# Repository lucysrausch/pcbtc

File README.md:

#PCB based MIDI Tesla Coil

For documentation, please see (and like ;) my Hackaday project: https://hackaday.io/project/165112-pcbtc-gan-edition

For the mainboard, please use V1.6 to order the pcbs. Select the pcb thickness to be as thin as possible, eg. 1mm.
For the current design you also need the bottom pcb coil (https://github.com/lucysrausch/pcbtc/tree/master/hardware/gerber_coil_01) and the top pcb coil (https://github.com/lucysrausch/pcbtc/tree/master/hardware/gerber_coil_04).
For these pcbs, please use 1.6mm thickness or thicker (eg. 2mm).

Check out the interactive html BOM for easier assembly: https://github.com/lucysrausch/pcbtc/blob/master/hardware/kicad/bom/ibom.html

Known bugs (V1.5):
* Missing pulldown for gatedriver input of the flyback converter
This can cause problems when in DFU mode as the mosfet might switch on permanently, shortying VUSB (Fixed in V1.6)
* Missing input decoupling capacitors underneath the LMG5200.
Adding additional high-quality 100pF and 100nF ceramic capacitors on the bottom of the pcb improves performance drastically (Fixed in V1.6)
* Unknown problem causes GaN module to fail when touching the arcs with the finger or a screwdriver.
The reson for this is unknown so far. Maybe EMI, maybe bad layout. Just don't touch the arcs for too long for now. Discharges to air work reliably. (Maybe fixed in V1.6 thanks to suggestions from nikisalli)

Flash with dfu-util -d 0483:df11 -a 0 -s 0x8000000:leave -D build/pcbtcMIDI.bin

Midi stack based on:
https://github.com/keshikan/CureMIDI 

## USB-MIDI Interface (2IN/2OUT) for STM32 "CureMIDI"

### Author

(c) 2018 Keshikan ( [Website](http://www.keshikan.net/),  [Twitter](https://twitter.com/keshinomi_88pro) )

### License

* USB MIDI Class Driver: [CC BY 4.0](https://creativecommons.org/licenses/by/4.0/)
* STM32 CubeF0: BSD-3-Clause based.
* Other Codes, Hardware, Schematic: [GPLv3](https://www.gnu.org/licenses/gpl-3.0.html)

See also [LICENSE.md](./LICENSE.md)

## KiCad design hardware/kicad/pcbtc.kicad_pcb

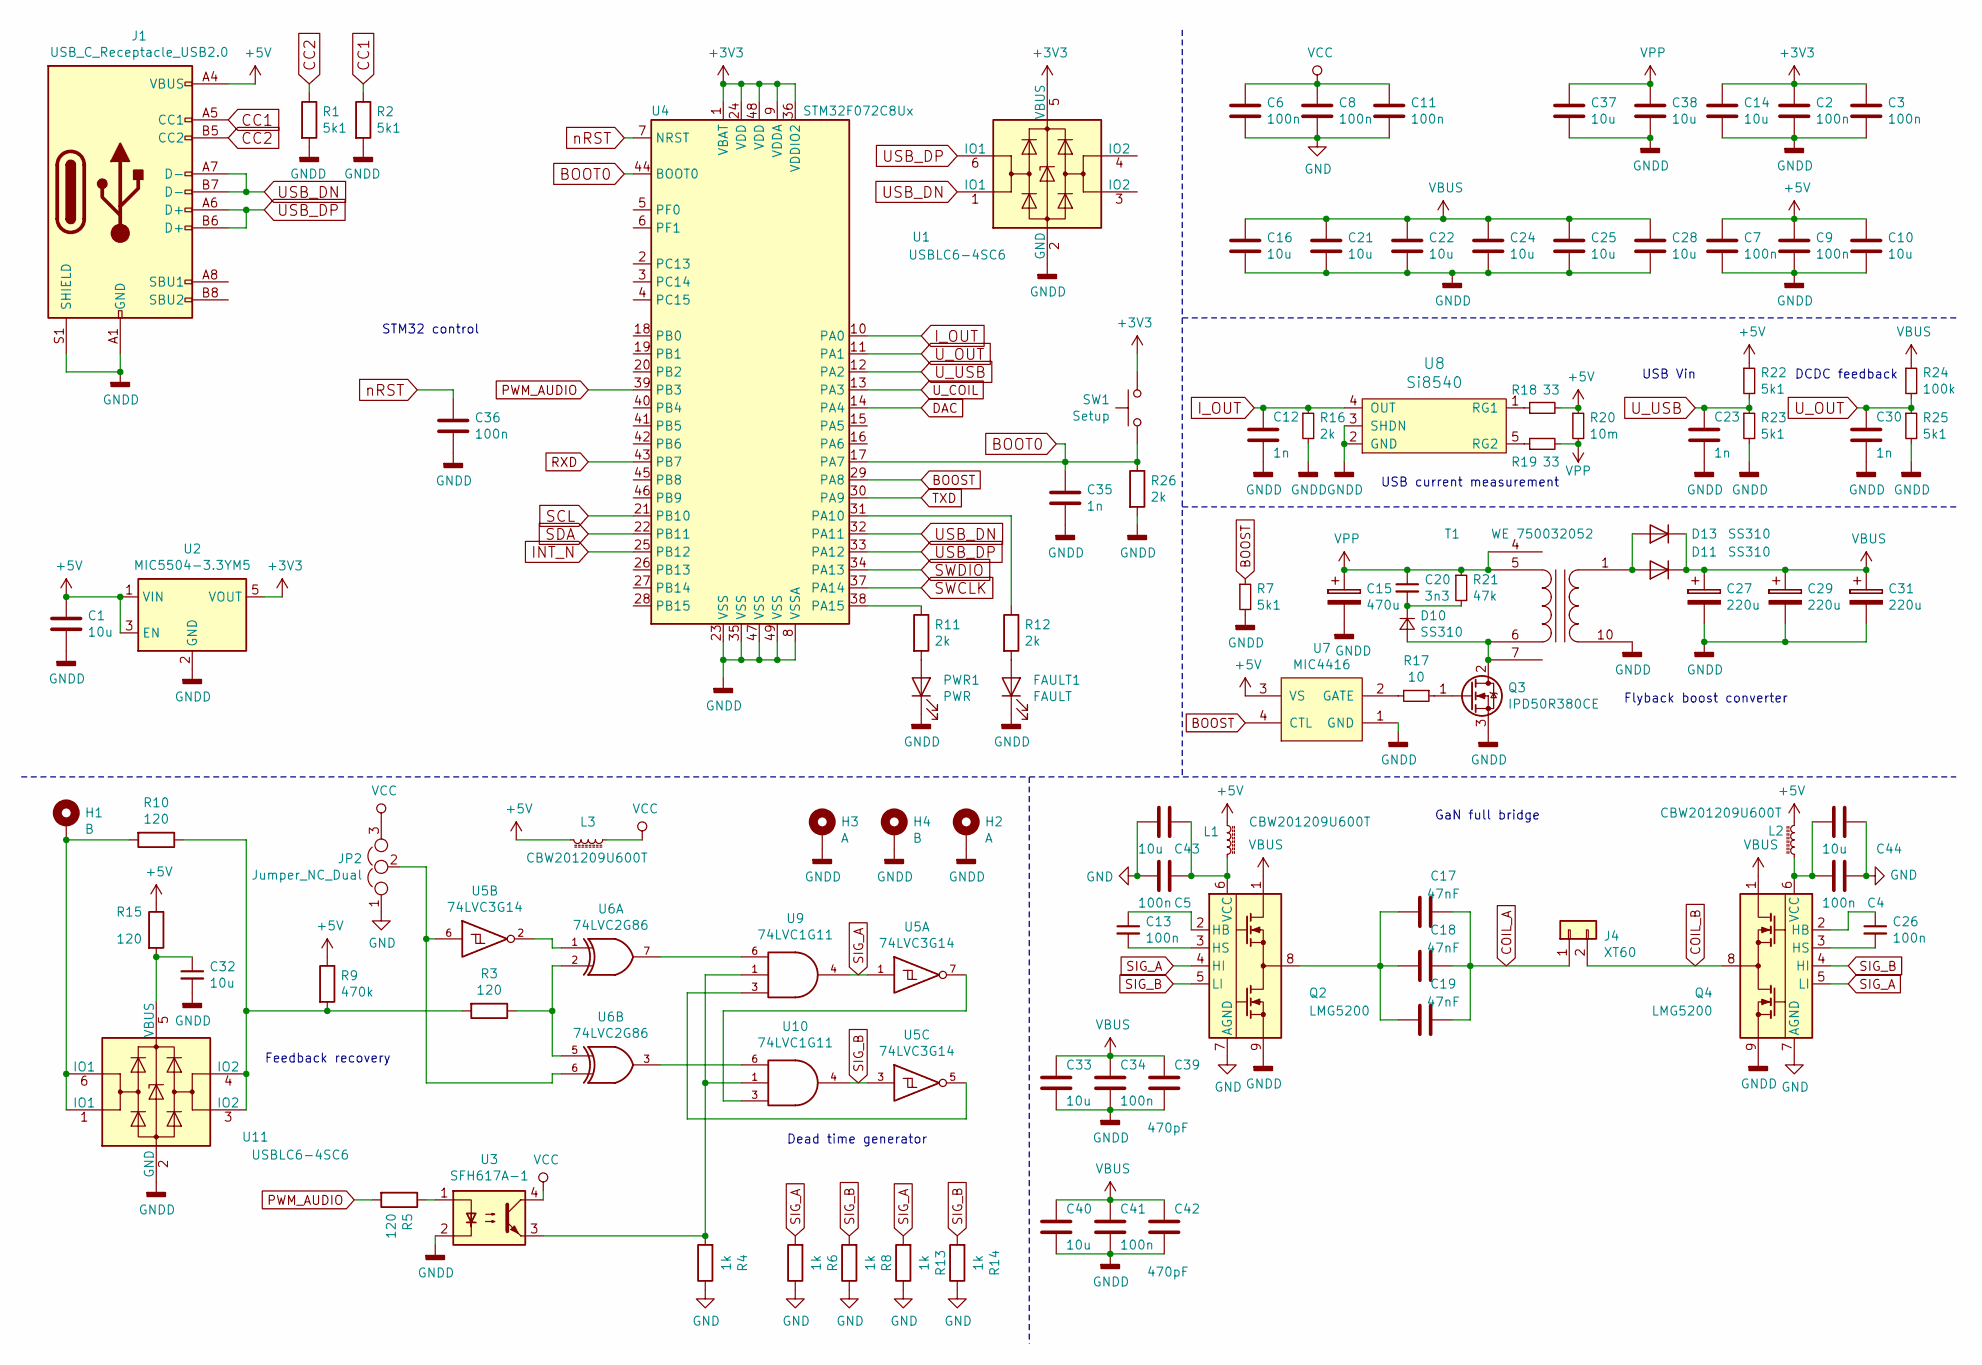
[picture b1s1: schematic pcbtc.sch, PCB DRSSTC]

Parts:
C1, C16, C21, C22, C24, C25, C28, C33, C37, C38, C40: 10u; C_1206_3216Metric
C2, C3, C4, C5, C6, C7, C8, C9, C11, C13, C26, C36: 100n; C_0603_1608Metric
C10, C14, C32, C43, C44: 10u; C_0603_1608Metric
C12, C23, C30, C35: 1n; C_0603_1608Metric
C15: 470u; C_Elec_10x10.2
C17, C18, C19: 47nF; C_Rect_L13.0mm_W6.5mm_P7.50mm_P10.00mm
C20: 3n3; C_1206_3216Metric
C27, C29, C31: 220u; C_Elec_10x10.2
C34, C41: 100n; C_1206_3216Metric
C39, C42: 470pF; C_1206_3216Metric
D10, D11, D13: SS310; D_SMA
FAULT1: FAULT; LED_0603_1608Metric
H1, H4: B; MountingHole_3.2mm_M3_Pad_Via
H2, H3: A; MountingHole_3.2mm_M3_Pad_Via
J1: USB_C_Receptacle_USB2.0; USB-C 16Pin
J4: XT60
JP2: Jumper_NC_Dual; SolderJumper-3_P1.3mm_Bridged12_RoundedPad1.0x1.5mm
L1, L2, L3: CBW201209U600T; L_0805_2012Metric
PWR1: PWR; LED_0603_1608Metric
Q2, Q4: LMG5200; Texas_MOF0009A
Q3: IPD50R380CE; TO-252-2
R1, R2: 5k1; C_0603_1608Metric
R3, R5, R10, R15: 120; R_0603_1608Metric
R4, R6, R8, R13, R14: 1k; R_0603_1608Metric
R7, R22, R23, R25: 5k1; R_0603_1608Metric
R9: 470k; R_0603_1608Metric
R11, R12, R16, R26: 2k; R_0603_1608Metric
R17: 10; R_0603_1608Metric
R18, R19: 33; R_0603_1608Metric
R20: 10m; R_1206_3216Metric
R21: 47k; R_1206_3216Metric
R24: 100k; R_0603_1608Metric
SW1: Setup; SW_SPST_EVQP7C
T1: WE 750032052; SignalCommunications-WE-FB3751_EFD20
U1, U11: USBLC6-4SC6; SOT-23-6
U2: MIC5504-3.3YM5; SOT-23-5
U3: SFH617A-1; DIP-4_W7.62mm_SMDSocket_SmallPads
U4: STM32F072C8Ux; QFN-48-1EP_7x7mm_P0.5mm_EP5.6x5.6mm
U5: 74LVC3G14; TSSOP-8_3x3mm_P0.65mm
U6: 74LVC2G86; TSSOP-8_3x3mm_P0.65mm
U7: MIC4416; SOT143-4P190_237X112L31X44N
U8: Si8540; SOT-23-5
U9, U10: 74LVC1G11; SOT-23-6

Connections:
+3V3: C2.1, C3.1, C14.1, SW1.1, U1.5 (VBUS), U2.5 (VOUT), U4.1 (VBAT), U4.9 (VDDA), U4.24 (VDD), U4.36 (VDDIO2), U4.48 (VDD)
+5V: C1.1, C7.1, C9.1, C10.1, J1.A4 (VBUS), J1.A9 (VBUS), J1.B4 (VBUS), J1.B9 (VBUS), L1.2, L2.2, L3.1, R9.1, R15.1, R18.2, R20.1, R22.1, U2.1 (VIN), U2.3 (EN), U7.3 (VS)
BOOST: R7.1, U4.29 (PA8), U7.4 (CTL)
BOOT0: C35.1, R26.1, SW1.2, U4.17 (PA7), U4.44 (BOOT0)
CC1: J1.A5 (CC1), R2.1
CC2: J1.B5 (CC2), R1.1
COIL_A: C17.1, C18.1, C19.1, J4.1
COIL_B: J4.2, Q4.8
DAC: U4.14 (PA4)
GND: C4.1, C5.2, C6.2, C8.2, C11.2, C43.2, C44.1, JP2.1, Q2.7 (AGND), Q4.7 (AGND), R4.1, R6.1, R8.1, R13.1, R14.1, U5.4 (GND), U6.4 (GND), U9.2 (GND), U10.2 (GND)
GNDD: C1.2, C2.2, C3.2, C7.2, C9.2, C10.2, C12.2, C14.2, C15.2, C16.2, C21.2, C22.2, C23.2, C24.2, C25.2, C27.2, C28.2, C29.2, C30.2, C31.2, C32.2, C33.2, C34.2, C35.2, C36.2, C37.2, C38.2, C39.2, C40.2, C41.2, C42.2, FAULT1.1 (K), H2.1, H3.1, H4.1, J1.A1 (GND), J1.A12 (GND), J1.B1 (GND), J1.B12 (GND), J1.S1 (SHIELD), PWR1.1 (K), Q2.9, Q3.3 (S), Q4.9, R1.2, R2.2, R7.2, R16.2, R23.2, R25.2, R26.2, T1.10 (SA), U1.2 (GND), U2.2 (GND), U3.2, U4.8 (VSSA), U4.23 (VSS), U4.35 (VSS), U4.47 (VSS), U4.49 (VSS), U7.1 (GND), U8.2 (GND), U8.3 (SHDN), U11.2 (GND)
INT_N: U4.25 (PB12)
I_OUT: C12.1, R16.1, U4.10 (PA0), U8.4 (OUT)
unnamed: C4.2, C44.2, L2.1, Q4.6 (VCC)
unnamed: C13.1, Q2.2 (HB)
unnamed: C13.2, Q2.3 (HS)
unnamed: C17.2, C18.2, C19.2, Q2.8
unnamed: C20.2, D10.1 (K), R21.2
unnamed: C26.1, Q4.2 (HB)
unnamed: C26.2, Q4.3 (HS)
unnamed: C32.1, R15.2, U11.5 (VBUS)
unnamed: C5.1, C43.1, L1.1, Q2.6 (VCC)
unnamed: D10.2 (A), Q3.2 (D), T1.6 (AB), T1.7
unnamed: D11.2 (A), D13.2 (A), T1.1 (SB)
unnamed: FAULT1.2 (A), R12.2
unnamed: H1.1, R10.2, U11.1 (IO1), U11.6 (IO1)
unnamed: JP2.2, U5.6, U6.6
unnamed: PWR1.2 (A), R11.2
unnamed: Q3.1 (G), R17.1
unnamed: R3.1, U6.2, U6.5
unnamed: R4.2, U3.3, U9.1, U10.1
unnamed: R5.1, U3.1
unnamed: R3.2, R9.2, R10.1, U11.3 (IO2), U11.4 (IO2)
unnamed: R11.1, U4.38 (PA15)
unnamed: R12.1, U4.31 (PA10)
unnamed: R17.2, U7.2 (GATE)
unnamed: R18.1, U8.1 (RG1)
unnamed: R19.1, U8.5 (RG2)
unnamed: U5.2, U6.1
unnamed: U5.5, U9.3
unnamed: U6.7, U9.6
unnamed: U5.7, U10.3
unnamed: U6.3, U10.6
PWM_AUDIO: R5.2, U4.39 (PB3)
RXD: U4.43 (PB7)
SCL: U4.21 (PB10)
SDA: U4.22 (PB11)
SIG_A: Q2.4 (HI), Q4.5 (LI), R6.2, R13.2, U5.1, U9.4
SIG_B: Q2.5 (LI), Q4.4 (HI), R8.2, R14.2, U5.3, U10.4
SWCLK: U4.37 (PA14)
SWDIO: U4.34 (PA13)
TXD: U4.30 (PA9)
USB_DN: J1.A7 (D-), J1.B7 (D-), U1.1 (IO1), U4.32 (PA11)
USB_DP: J1.A6 (D+), J1.B6 (D+), U1.6 (IO1), U4.33 (PA12)
U_COIL: U4.13 (PA3)
U_OUT: C30.1, R24.2, R25.1, U4.11 (PA1)
U_USB: C23.1, R22.2, R23.1, U4.12 (PA2)
VBUS: C16.1, C21.1, C22.1, C24.1, C25.1, C27.1, C28.1, C29.1, C31.1, C33.1, C34.1, C39.1, C40.1, C41.1, C42.1, D11.1 (K), D13.1 (K), Q2.1, Q4.1, R24.1
VCC: C6.1, C8.1, C11.1, JP2.3, L3.2, U3.4, U5.8 (VCC), U6.8 (VCC), U9.5 (VCC), U10.5 (VCC)
VPP: C15.1, C20.1, C37.1, C38.1, R19.2, R20.2, R21.1, T1.4, T1.5 (AA)
nRST: C36.1, U4.7 (NRST)

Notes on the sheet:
Feedback recovery
Dead time generator
GaN full bridge
Flyback boost converter
USB current measurement
DCDC feedback
USB Vin
STM32 control

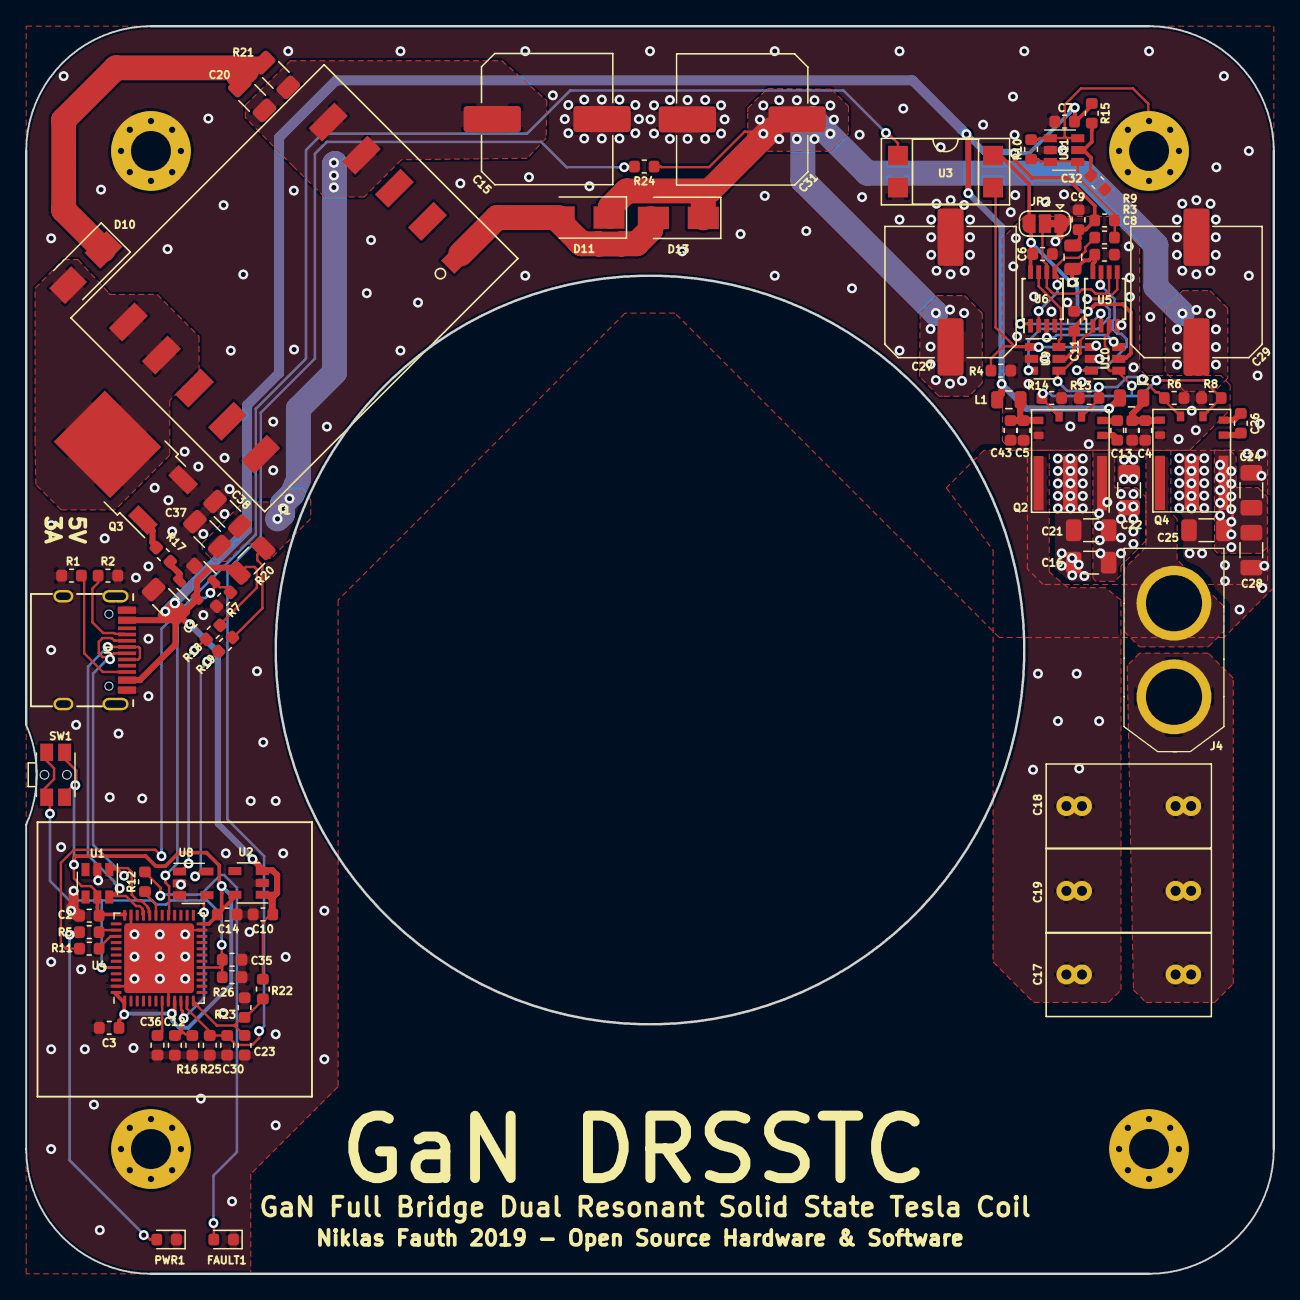
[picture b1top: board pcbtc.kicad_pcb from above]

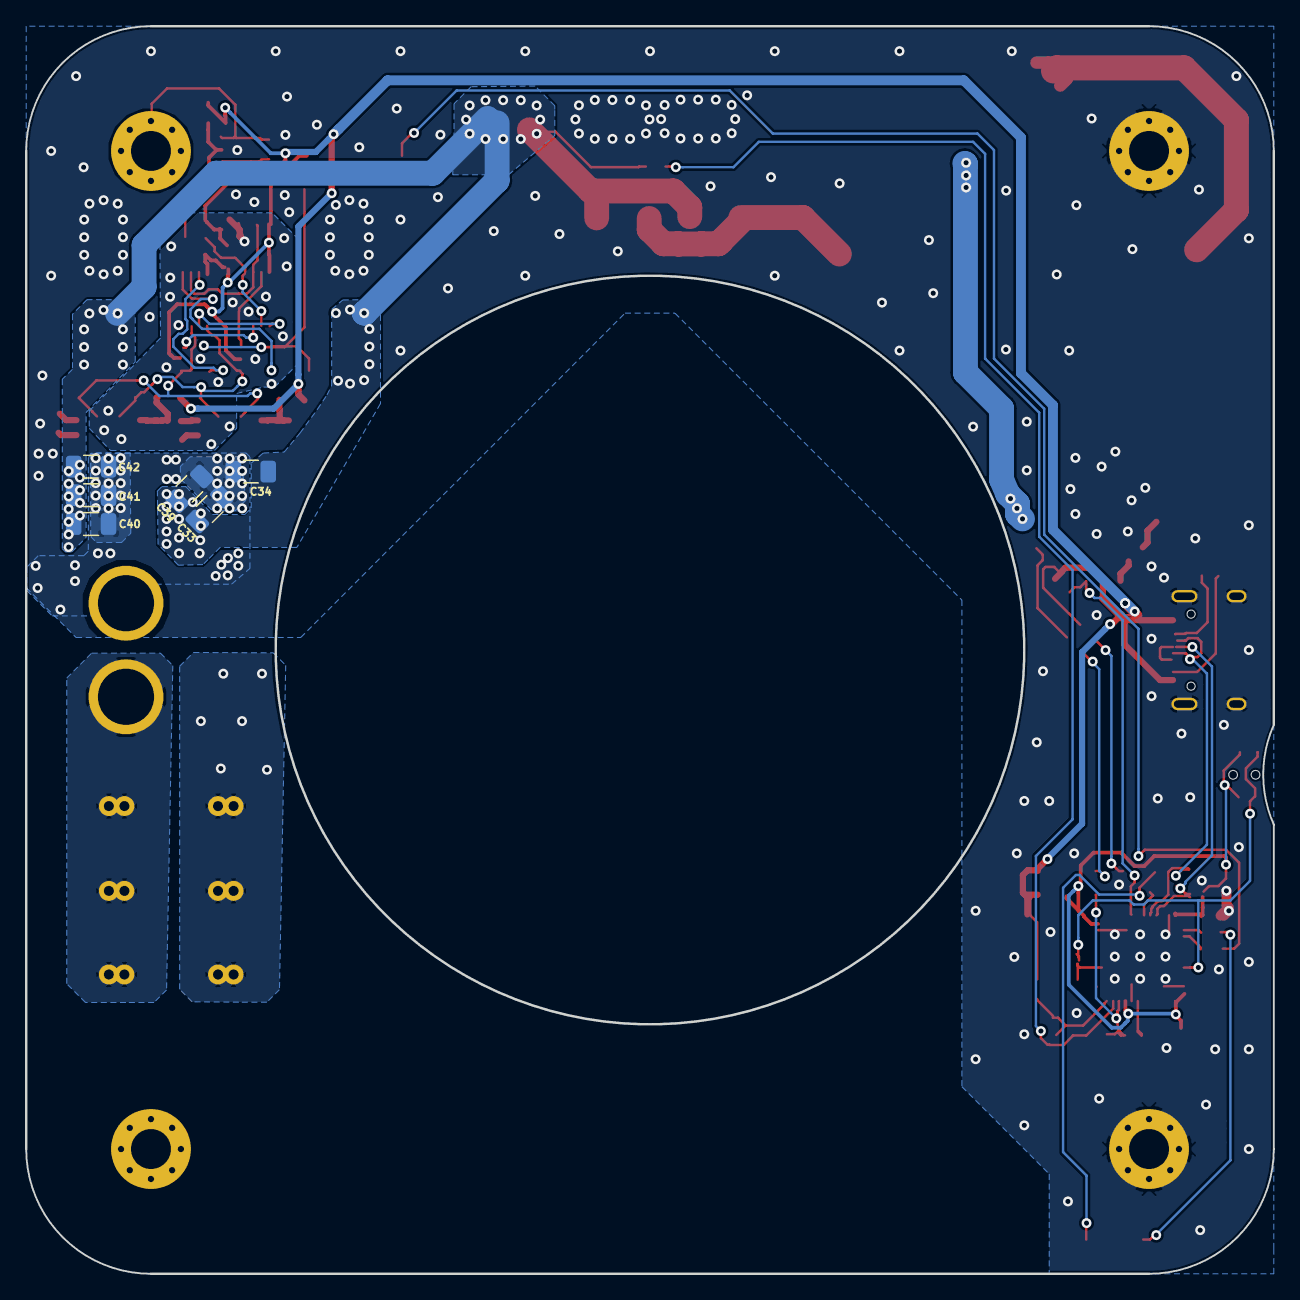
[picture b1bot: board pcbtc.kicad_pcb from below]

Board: 2 copper layers, 100.0 x 100.0 mm, 101 parts (6 on the bottom side), 52 nets.

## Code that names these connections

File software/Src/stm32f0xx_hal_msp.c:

/**
  ******************************************************************************
  * File Name          : stm32f0xx_hal_msp.c
  * Description        : This file provides code for the MSP Initialization
  *                      and de-Initialization codes.
  ******************************************************************************
  * This notice applies to any and all portions of this file
  * that are not between comment pairs USER CODE BEGIN and
  * USER CODE END. Other portions of this file, whether
  * inserted by the user or by software development tools
  * are owned by their respective copyright owners.
  *
  * Copyright (c) 2018 STMicroelectronics International N.V.
  * All rights reserved.
  *
  * Redistribution and use in source and binary forms, with or without
  * modification, are permitted, provided that the following conditions are met:
  *
  * 1. Redistribution of source code must retain the above copyright notice,
  *    this list of conditions and the following disclaimer.
  * 2. Redistributions in binary form must reproduce the above copyright notice,
  *    this list of conditions and the following disclaimer in the documentation
  *    and/or other materials provided with the distribution.
  * 3. Neither the name of STMicroelectronics nor the names of other
  *    contributors to this software may be used to endorse or promote products
  *    derived from this software without specific written permission.
  * 4. This software, including modifications and/or derivative works of this
  *    software, must execute solely and exclusively on microcontroller or
  *    microprocessor devices manufactured by or for STMicroelectronics.
  * 5. Redistribution and use of this software other than as permitted under
  *    this license is void and will automatically terminate your rights under
  *    this license.
  *
  * THIS SOFTWARE IS PROVIDED BY STMICROELECTRONICS AND CONTRIBUTORS "AS IS"
  * AND ANY EXPRESS, IMPLIED OR STATUTORY WARRANTIES, INCLUDING, BUT NOT
  * LIMITED TO, THE IMPLIED WARRANTIES OF MERCHANTABILITY, FITNESS FOR A
  * PARTICULAR PURPOSE AND NON-INFRINGEMENT OF THIRD PARTY INTELLECTUAL PROPERTY
  * RIGHTS ARE DISCLAIMED TO THE FULLEST EXTENT PERMITTED BY LAW. IN NO EVENT
  * SHALL STMICROELECTRONICS OR CONTRIBUTORS BE LIABLE FOR ANY DIRECT, INDIRECT,
  * INCIDENTAL, SPECIAL, EXEMPLARY, OR CONSEQUENTIAL DAMAGES (INCLUDING, BUT NOT
  * LIMITED TO, PROCUREMENT OF SUBSTITUTE GOODS OR SERVICES; LOSS OF USE, DATA,
  * OR PROFITS; OR BUSINESS INTERRUPTION) HOWEVER CAUSED AND ON ANY THEORY OF
  * LIABILITY, WHETHER IN CONTRACT, STRICT LIABILITY, OR TORT (INCLUDING
  * NEGLIGENCE OR OTHERWISE) ARISING IN ANY WAY OUT OF THE USE OF THIS SOFTWARE,
  * EVEN IF ADVISED OF THE POSSIBILITY OF SUCH DAMAGE.
  *
  ******************************************************************************
  */
/* Includes ------------------------------------------------------------------*/
#include "stm32f0xx_hal.h"

extern DMA_HandleTypeDef hdma_usart1_rx;

extern DMA_HandleTypeDef hdma_usart2_rx;

extern DMA_HandleTypeDef hdma_adc;

extern void _Error_Handler(char *, int);
/* USER CODE BEGIN 0 */

/* USER CODE END 0 */
/**
  * Initializes the Global MSP.
  */
void HAL_MspInit(void)
{
  /* USER CODE BEGIN MspInit 0 */

  /* USER CODE END MspInit 0 */

  __HAL_RCC_SYSCFG_CLK_ENABLE();
  __HAL_RCC_PWR_CLK_ENABLE();

  /* System interrupt init*/
  /* SVC_IRQn interrupt configuration */
  HAL_NVIC_SetPriority(SVC_IRQn, 0, 0);
  /* PendSV_IRQn interrupt configuration */
  HAL_NVIC_SetPriority(PendSV_IRQn, 0, 0);
  /* SysTick_IRQn interrupt configuration */
  HAL_NVIC_SetPriority(SysTick_IRQn, 0, 0);

  /* USER CODE BEGIN MspInit 1 */

  /* USER CODE END MspInit 1 */
}



void HAL_TIM_Base_MspInit(TIM_HandleTypeDef* htim_base)
{

  if(htim_base->Instance==TIM17)
  {
  /* USER CODE BEGIN TIM17_MspInit 0 */

  /* USER CODE END TIM17_MspInit 0 */
    /* Peripheral clock enable */
    __HAL_RCC_TIM17_CLK_ENABLE();
    /* TIM17 interrupt Init */
    HAL_NVIC_SetPriority(TIM17_IRQn, 2, 0);
    HAL_NVIC_EnableIRQ(TIM17_IRQn);
  /* USER CODE BEGIN TIM17_MspInit 1 */

  /* USER CODE END TIM17_MspInit 1 */
  }
  if(htim_base->Instance==TIM14)
  {
  /* USER CODE BEGIN TIM17_MspInit 0 */

  /* USER CODE END TIM17_MspInit 0 */
    /* Peripheral clock enable */
    __HAL_RCC_TIM14_CLK_ENABLE();
    /* TIM17 interrupt Init */
    HAL_NVIC_SetPriority(TIM14_IRQn, 2, 0);
    HAL_NVIC_EnableIRQ(TIM14_IRQn);
  /* USER CODE BEGIN TIM17_MspInit 1 */

  /* USER CODE END TIM17_MspInit 1 */
  }
  if(htim_base->Instance==TIM15)
  {
  /* USER CODE BEGIN TIM17_MspInit 0 */

  /* USER CODE END TIM17_MspInit 0 */
    /* Peripheral clock enable */
    __HAL_RCC_TIM15_CLK_ENABLE();
    /* TIM17 interrupt Init */
    HAL_NVIC_SetPriority(TIM15_IRQn, 2, 0);
    HAL_NVIC_EnableIRQ(TIM15_IRQn);
  /* USER CODE BEGIN TIM17_MspInit 1 */

  /* USER CODE END TIM17_MspInit 1 */
  }
  if(htim_base->Instance==TIM17)
  {
  /* USER CODE BEGIN TIM17_MspInit 0 */

  /* USER CODE END TIM17_MspInit 0 */
    /* Peripheral clock enable */
    __HAL_RCC_TIM17_CLK_ENABLE();
    /* TIM17 interrupt Init */
    HAL_NVIC_SetPriority(TIM17_IRQn, 2, 0);
    HAL_NVIC_EnableIRQ(TIM17_IRQn);
  /* USER CODE BEGIN TIM17_MspInit 1 */

  /* USER CODE END TIM17_MspInit 1 */
  }
  if(htim_base->Instance==TIM2)
  {
  /* USER CODE BEGIN TIM4_MspInit 0 */

  /* USER CODE END TIM4_MspInit 0 */
    /* Peripheral clock enable */
    __HAL_RCC_TIM2_CLK_ENABLE();
  /* USER CODE BEGIN TIM4_MspInit 1 */

  /* USER CODE END TIM4_MspInit 1 */
  }

  if(htim_base->Instance==TIM1)
  {
  /* USER CODE BEGIN TIM4_MspInit 0 */

  /* USER CODE END TIM4_MspInit 0 */
    /* Peripheral clock enable */
    __HAL_RCC_TIM1_CLK_ENABLE();

  /* USER CODE BEGIN TIM4_MspInit 1 */

  /* USER CODE END TIM4_MspInit 1 */
  }

}



void HAL_TIM_Base_MspDeInit(TIM_HandleTypeDef* htim_base)
{

  if(htim_base->Instance==TIM17)
  {
  /* USER CODE BEGIN TIM17_MspDeInit 0 */

  /* USER CODE END TIM17_MspDeInit 0 */
    /* Peripheral clock disable */
    __HAL_RCC_TIM17_CLK_DISABLE();

    /* TIM17 interrupt DeInit */
    HAL_NVIC_DisableIRQ(TIM17_IRQn);
  /* USER CODE BEGIN TIM17_MspDeInit 1 */

  /* USER CODE END TIM17_MspDeInit 1 */
  }

}


void HAL_TIM_MspPostInit(TIM_HandleTypeDef* htim)
{

  GPIO_InitTypeDef GPIO_InitStruct;
  if(htim->Instance==TIM2)
  {
  /* USER CODE BEGIN TIM4_MspPostInit 0 */

  /* USER CODE END TIM4_MspPostInit 0 */

    /**TIM4 GPIO Configuration
    PB6     ------> TIM4_CH1
    */
    GPIO_InitStruct.Pin = GPIO_PIN_3;
    GPIO_InitStruct.Mode = GPIO_MODE_AF_PP;
    GPIO_InitStruct.Speed = GPIO_SPEED_FREQ_HIGH;
    GPIO_InitStruct.Alternate = GPIO_AF2_TIM2;
    HAL_GPIO_Init(GPIOB, &GPIO_InitStruct);

    HAL_NVIC_SetPriority(TIM2_IRQn, 2, 0);
    HAL_NVIC_EnableIRQ(TIM2_IRQn);

  /* USER CODE BEGIN TIM4_MspPostInit 1 */

  /* USER CODE END TIM4_MspPostInit 1 */
  }

  else if(htim->Instance==TIM1)
  {
  /* USER CODE BEGIN TIM1_MspPostInit 0 */

  /* USER CODE END TIM1_MspPostInit 0 */
    /**TIM1 GPIO Configuration
    PA8     ------> TIM1_CH1
    */
    GPIO_InitStruct.Pin = GPIO_PIN_8;
    GPIO_InitStruct.Mode = GPIO_MODE_AF_PP;
    GPIO_InitStruct.Pull = GPIO_PULLDOWN;
    GPIO_InitStruct.Speed = GPIO_SPEED_FREQ_HIGH;
    GPIO_InitStruct.Alternate = GPIO_AF2_TIM1;
    HAL_GPIO_Init(GPIOA, &GPIO_InitStruct);

  /* USER CODE BEGIN TIM1_MspPostInit 1 */

  /* USER CODE END TIM1_MspPostInit 1 */
  }
}

void HAL_ADC_MspInit(ADC_HandleTypeDef* hadc)
{

  GPIO_InitTypeDef GPIO_InitStruct;
  if(hadc->Instance==ADC1)
  {
  /* USER CODE BEGIN ADC1_MspInit 0 */

  /* USER CODE END ADC1_MspInit 0 */
    /* Peripheral clock enable */
    __HAL_RCC_ADC1_CLK_ENABLE();

    /**ADC GPIO Configuration
    PA0     ------> ADC_IN0
    PA1     ------> ADC_IN1
    PA2     ------> ADC_IN2
    PA3     ------> ADC_IN3
    */
    GPIO_InitStruct.Pin = GPIO_PIN_0|GPIO_PIN_1|GPIO_PIN_2;
    GPIO_InitStruct.Mode = GPIO_MODE_ANALOG;
    GPIO_InitStruct.Pull = GPIO_NOPULL;
    HAL_GPIO_Init(GPIOA, &GPIO_InitStruct);

    /* ADC1 DMA Init */
    /* ADC Init */
    hdma_adc.Instance = DMA1_Channel1;
    hdma_adc.Init.Direction = DMA_PERIPH_TO_MEMORY;
    hdma_adc.Init.PeriphInc = DMA_PINC_DISABLE;
    hdma_adc.Init.MemInc = DMA_MINC_ENABLE;
    hdma_adc.Init.PeriphDataAlignment = DMA_PDATAALIGN_HALFWORD;
    hdma_adc.Init.MemDataAlignment = DMA_MDATAALIGN_HALFWORD;
    hdma_adc.Init.Mode = DMA_CIRCULAR;
    hdma_adc.Init.Priority = DMA_PRIORITY_LOW;
    if (HAL_DMA_Init(&hdma_adc) != HAL_OK)
    {
      _Error_Handler(__FILE__, __LINE__);
    }

    __HAL_LINKDMA(hadc,DMA_Handle,hdma_adc);

  /* USER CODE BEGIN ADC1_MspInit 1 */

  /* USER CODE END ADC1_MspInit 1 */
  }

}



/* USER CODE BEGIN 1 */

/* USER CODE END 1 */

/**
  * @}
  */

/**
  * @}
  */

/************************ (C) COPYRIGHT STMicroelectronics *****END OF FILE****/

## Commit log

2018-07-08 modified readme
2018-07-08 modified LICENSE.md
2018-07-08 Modified readme. Updated schematic.
2018-12-02 woriking with single timer 2 in OC mode
2018-12-02 pcbtc: Initial commit
2018-12-21 UPD: schematics
2018-12-21 ADD: schematics
2019-04-13 V1.2 wroking release
2019-04-13 added cdc
2019-04-20 ADD: schematics and kicad project
2019-04-22 pretty schematics
2019-04-22 Added known bugs
2019-04-25 Changed the STM32 QFN to an LQFP, easier to handle
2019-04-25 Fixed DRC errors
2019-04-25 Previous component position caused some shorts to the can
2019-04-25 Added keepout zones in the can pads
2019-04-25 Improved components refs readability for the microcontroller section
2019-04-27 Released V1.6 gerber
2019-04-27 FIX: interactive html bom capacitor values
2019-10-16 ADD: build instructions
2020-05-03 Fix handling of zero velocity note on messages
2022-10-19 Fix bug that the Coil coudn't play back the same tone twice
